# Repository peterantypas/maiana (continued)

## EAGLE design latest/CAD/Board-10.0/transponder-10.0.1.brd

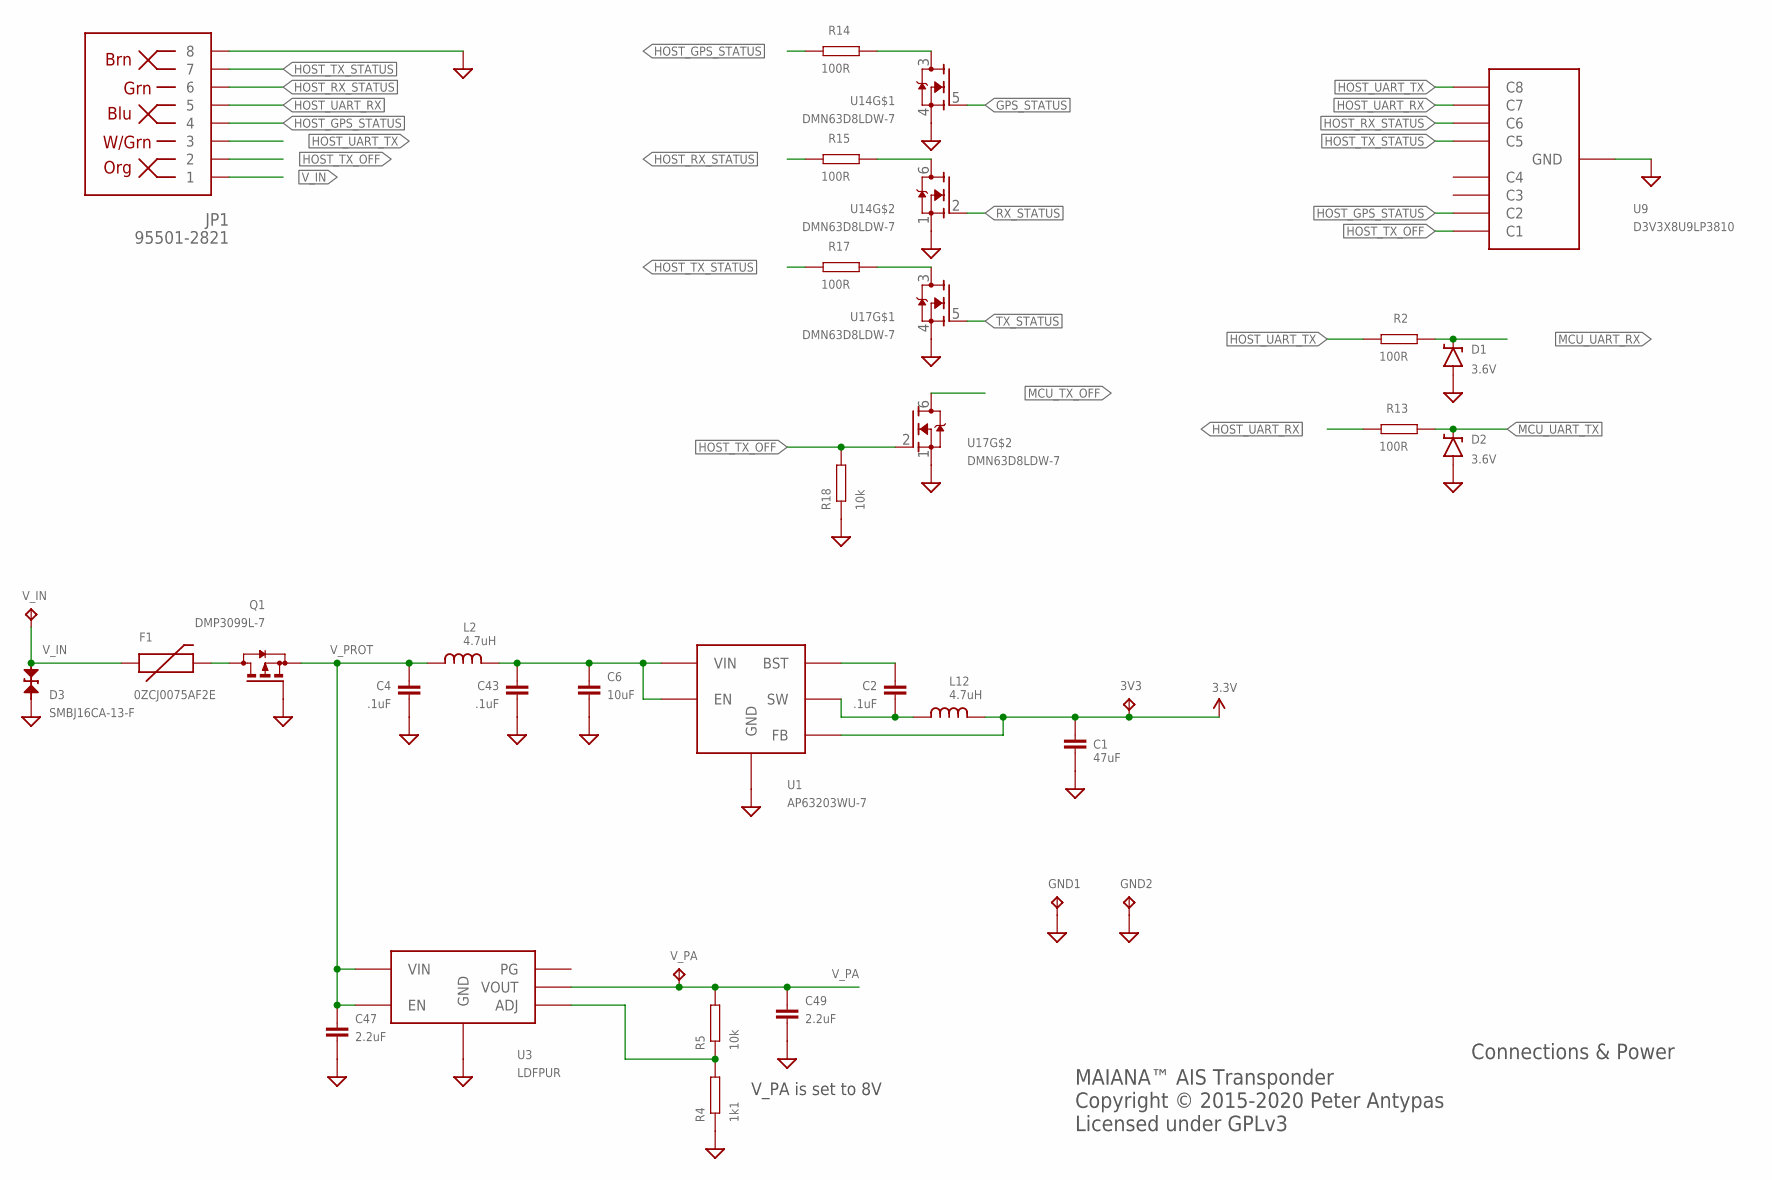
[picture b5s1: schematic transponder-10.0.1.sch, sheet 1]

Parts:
3V3: TPTP12R; TP12R
C1: 47uF; 1206; PARTNO CL31A476MQHNNNE
C2, C4, C43: .1uF; 0603; PARTNO EMK107B7104KAHT
C6: 10uF; 0805; PARTNO EMK212ABJ106KG-T
C47, C49: 2.2uF; 0603; PARTNO EMK107BJ225KA-T
D1, D2: 3.6V; SOD-323; PARTNO MM3Z3V6C
D3: SMBJ16CA-13-F; SMB-BIDIR; PARTNO SMBJ16CA-13-F
F1: 0ZCJ0075AF2E; PTC-1206; PARTNO 0ZCJ0075AF2E
GND1, GND2: TPTP12R; TP12R
JP1: 95501-2821; RJ45-8; PARTNO 95501-2821
L2, L12: 4.7uH; 0805; PARTNO MLZ2012M4R7WT000
Q1: DMP3099L-7; SOT23; PARTNO DMP3099L-7
R2, R13, R14, R15, R17: 100R; 0603; PARTNO RC0603JR-07100RL
R4: 1k1; 0603; PARTNO RC0603JR-071K1L
R5, R18: 10k; 0603; PARTNO RC0603JR-0710KL
U1: AP63203WU-7; SOT23-6
U3: LDFPUR; DFN-6; PARTNO LDFPUR
U9: D3V3X8U9LP3810; U-DFN3810-9(B)
U14, U17: DMN63D8LDW-7; SOT363; PARTNO DMN63D8LDW-7
V_IN: TPTP12R; TP12R
V_PA: TPTP12R; TP12R

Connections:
3.3V: 3V3.TP, C1.P$1 (1), L12.P$2 (2), U1.1 (FB); also elsewhere on the board
BST: C2.P$1 (1), U1.6 (BST)
GND: C1.P$2 (2), C4.P$2 (2), C6.P$2 (2), C43.P$2 (2), C47.P$2 (2), C49.P$2 (2), D1.A, D2.A, D3.C, GND1.TP, GND2.TP, JP1.8, Q1.1 (G), R4.P$1, R18.P$1, U1.4 (GND), U3.P$4 (GND), U3.P$7 (GND), U9.P$3 (GND), U14.1 (S), U14.4 (S), U17.1 (S), U17.4 (S); also elsewhere on the board
GPS_STATUS: U14.5 (G); also elsewhere on the board
HOST_GPS_STATUS: JP1.4, R14.P$2, U9.P$2 (C2)
HOST_RX_STATUS: JP1.6, R15.P$2, U9.P$7 (C6)
HOST_TX_OFF: JP1.2, R18.P$2, U9.P$1 (C1), U17.2 (G)
HOST_TX_STATUS: JP1.7, R17.P$2, U9.P$6 (C5)
HOST_UART_RX: JP1.5, R13.P$2, U9.P$8 (C7)
HOST_UART_TX: JP1.3, R2.P$2, U9.P$9 (C8)
MCU_TX_OFF: U17.6 (D); also elsewhere on the board
MCU_UART_RX: D1.C, R2.P$1; also elsewhere on the board
MCU_UART_TX: D2.C, R13.P$1; also elsewhere on the board
unnamed: R14.P$1, U14.3 (D)
unnamed: R15.P$1, U14.6 (D)
unnamed: R17.P$1, U17.3 (D)
unnamed: C6.P$1 (1), C43.P$1 (1), L2.P$2 (2), U1.2 (EN), U1.3 (VIN)
unnamed: R4.P$2, R5.P$1, U3.P$2 (ADJ)
unnamed: F1.2, Q1.3 (D)
RX_STATUS: U14.2 (G); also elsewhere on the board
SW: C2.P$2 (2), L12.P$1 (1), U1.5 (SW)
TX_STATUS: U17.5 (G); also elsewhere on the board
V_IN: D3.A, F1.1, JP1.1, V_IN.TP
V_PA: C49.P$1 (1), R5.P$2, U3.P$1 (VOUT), V_PA.TP; also elsewhere on the board
V_PROT: C4.P$1 (1), C47.P$1 (1), L2.P$1 (1), Q1.2 (S), U3.P$5 (EN), U3.P$6 (VIN)

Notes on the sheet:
Connections & Power
MAIANA™ AIS Transponder Copyright © 2015-2020 Peter Antypas Licensed under GPLv3
V_PA is set to 8V

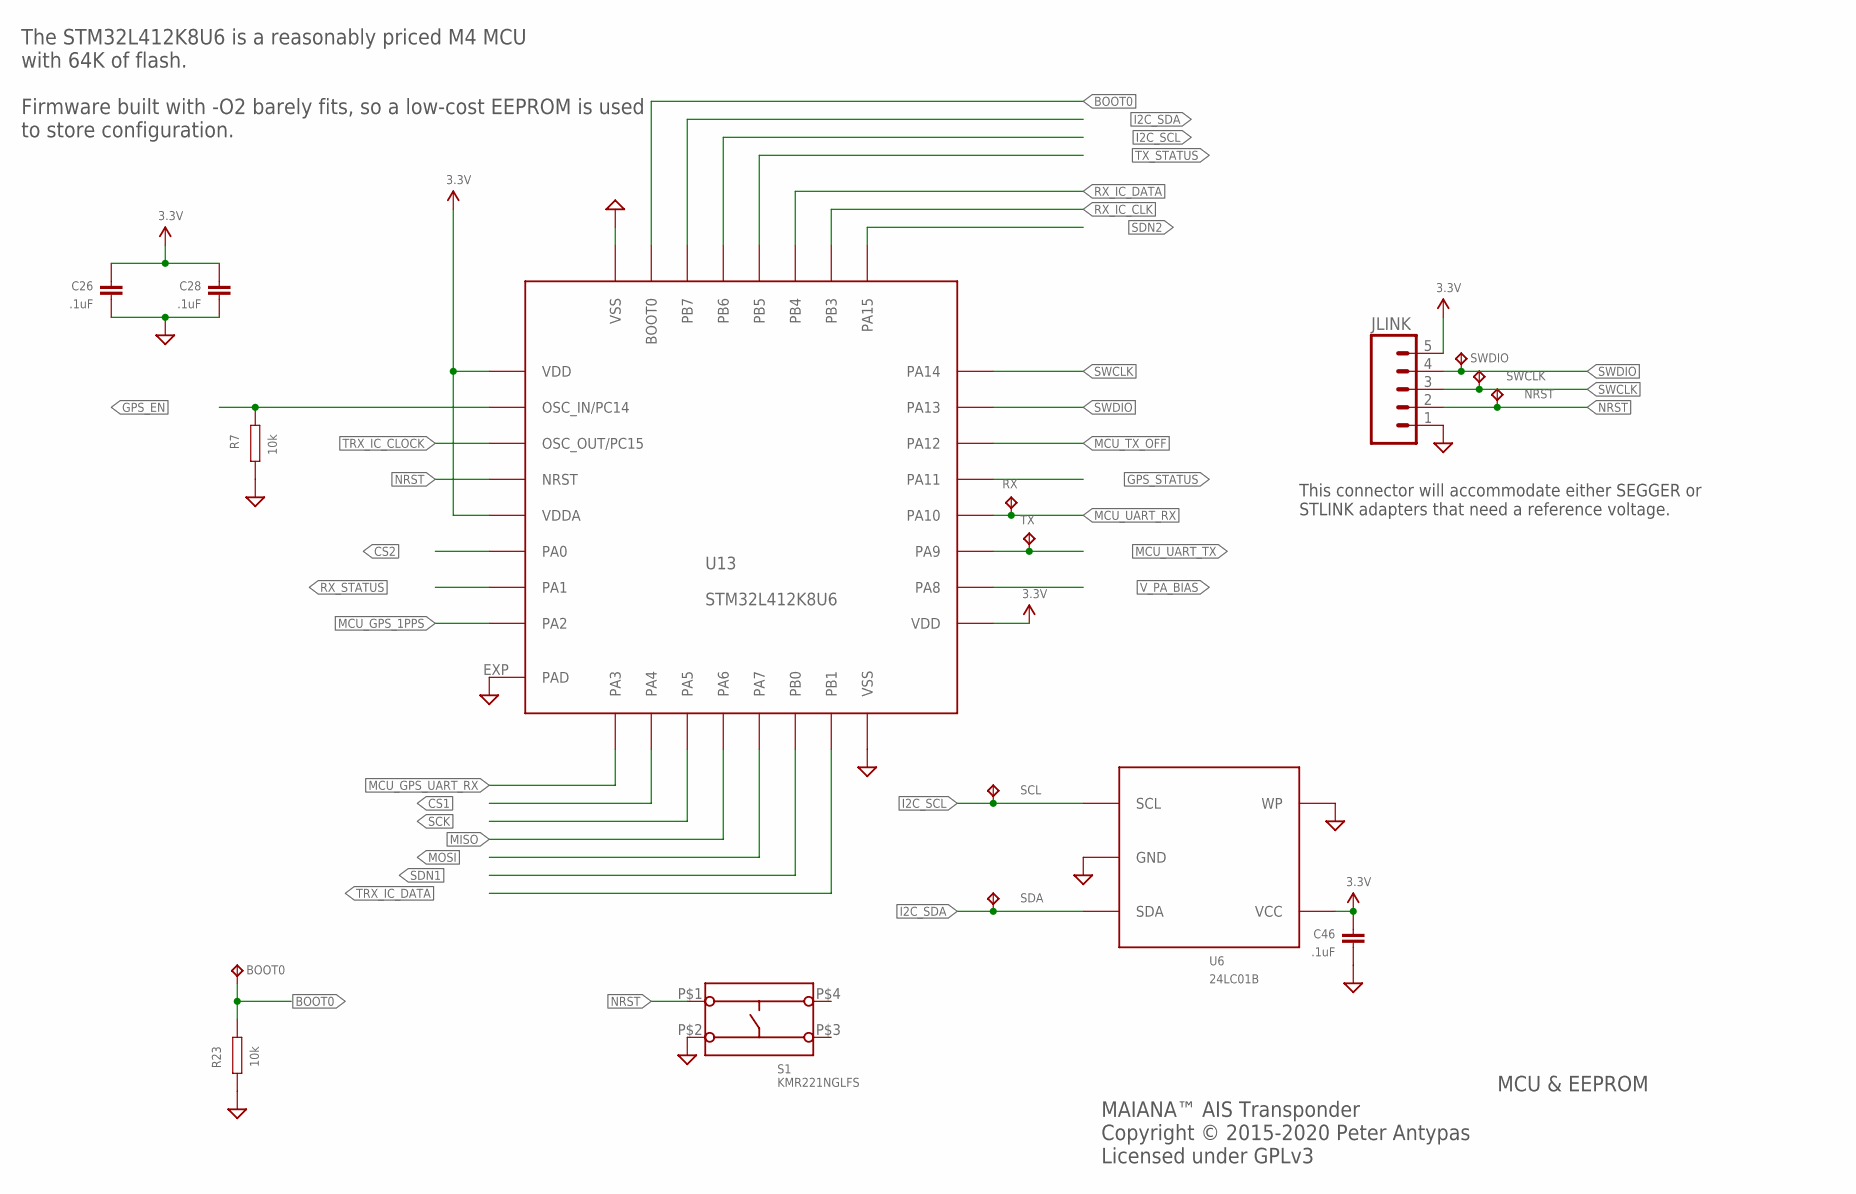
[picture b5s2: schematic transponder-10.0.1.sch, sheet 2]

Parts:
BOOT0: TPTP12R; TP12R
C26, C28, C46: .1uF; 0603; PARTNO EMK107B7104KAHT
JLINK: M05PTH; 1X05
NRST: TPTP12R; TP12R
R7, R23: 10k; 0603; PARTNO RC0603JR-0710KL
RX: TPTP12R; TP12R
S1: KMR221NGLFS
SCL: TPTP12R; TP12R
SDA: TPTP12R; TP12R
SWCLK: TPTP12R; TP12R
SWDIO: TPTP12R; TP12R
TX: TPTP12R; TP12R
U6: 24LC01B; SOT23-5; PARTNO 24LC01BT-I/OT
U13: STM32L412K8U6; QFN32; PARTNO STM32L412K8U6

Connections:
3.3V: C26.P$1 (1), C28.P$1 (1), C46.P$1 (1), JLINK.5, U6.4 (VCC), U13.1 (VDD), U13.5 (VDDA), U13.17 (VDD); also elsewhere on the board
BOOT0: BOOT0.TP, R23.P$1, U13.31 (BOOT0)
CS1: U13.10 (PA4); also elsewhere on the board
CS2: U13.6 (PA0); also elsewhere on the board
GND: C26.P$2 (2), C28.P$2 (2), C46.P$2 (2), JLINK.1, R7.P$2, R23.P$2, S1.P$2 (S2), U6.2 (GND), U6.5 (WP), U13.16 (VSS), U13.32 (VSS), U13.EXP (PAD); also elsewhere on the board
GPS_EN: R7.P$1, U13.2 (OSC_IN/PC14); also elsewhere on the board
GPS_STATUS: U13.21 (PA11); also elsewhere on the board
I2C_SCL: SCL.TP, U6.1 (SCL), U13.29 (PB6)
I2C_SDA: SDA.TP, U6.3 (SDA), U13.30 (PB7)
MCU_GPS_1PPS: U13.8 (PA2); also elsewhere on the board
MCU_GPS_UART_RX: U13.9 (PA3); also elsewhere on the board
MCU_TX_OFF: U13.22 (PA12); also elsewhere on the board
MCU_UART_RX: RX.TP, U13.20 (PA10); also elsewhere on the board
MCU_UART_TX: TX.TP, U13.19 (PA9); also elsewhere on the board
MISO: U13.12 (PA6); also elsewhere on the board
MOSI: U13.13 (PA7); also elsewhere on the board
NRST: JLINK.2, NRST.TP, S1.P$1 (S1), U13.4 (NRST)
RX_IC_CLK: U13.26 (PB3); also elsewhere on the board
RX_IC_DATA: U13.27 (PB4); also elsewhere on the board
RX_STATUS: U13.7 (PA1); also elsewhere on the board
SCK: U13.11 (PA5); also elsewhere on the board
SDN1: U13.14 (PB0); also elsewhere on the board
SDN2: U13.25 (PA15); also elsewhere on the board
SWCLK: JLINK.3, SWCLK.TP, U13.24 (PA14)
SWDIO: JLINK.4, SWDIO.TP, U13.23 (PA13)
TRX_IC_CLOCK: U13.3 (OSC_OUT/PC15); also elsewhere on the board
TRX_IC_DATA: U13.15 (PB1); also elsewhere on the board
TX_STATUS: U13.28 (PB5); also elsewhere on the board
V_PA_BIAS: U13.18 (PA8); also elsewhere on the board

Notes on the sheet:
MCU & EEPROM
MAIANA™ AIS Transponder Copyright © 2015-2020 Peter Antypas Licensed under GPLv3
The STM32L412K8U6 is a reasonably priced M4 MCU with 64K of flash. Firmware built with -O2 barely fits, so a low-cost EEPROM is used to store configuration.
This connector will accommodate either SEGGER or STLINK adapters that need a reference voltage.

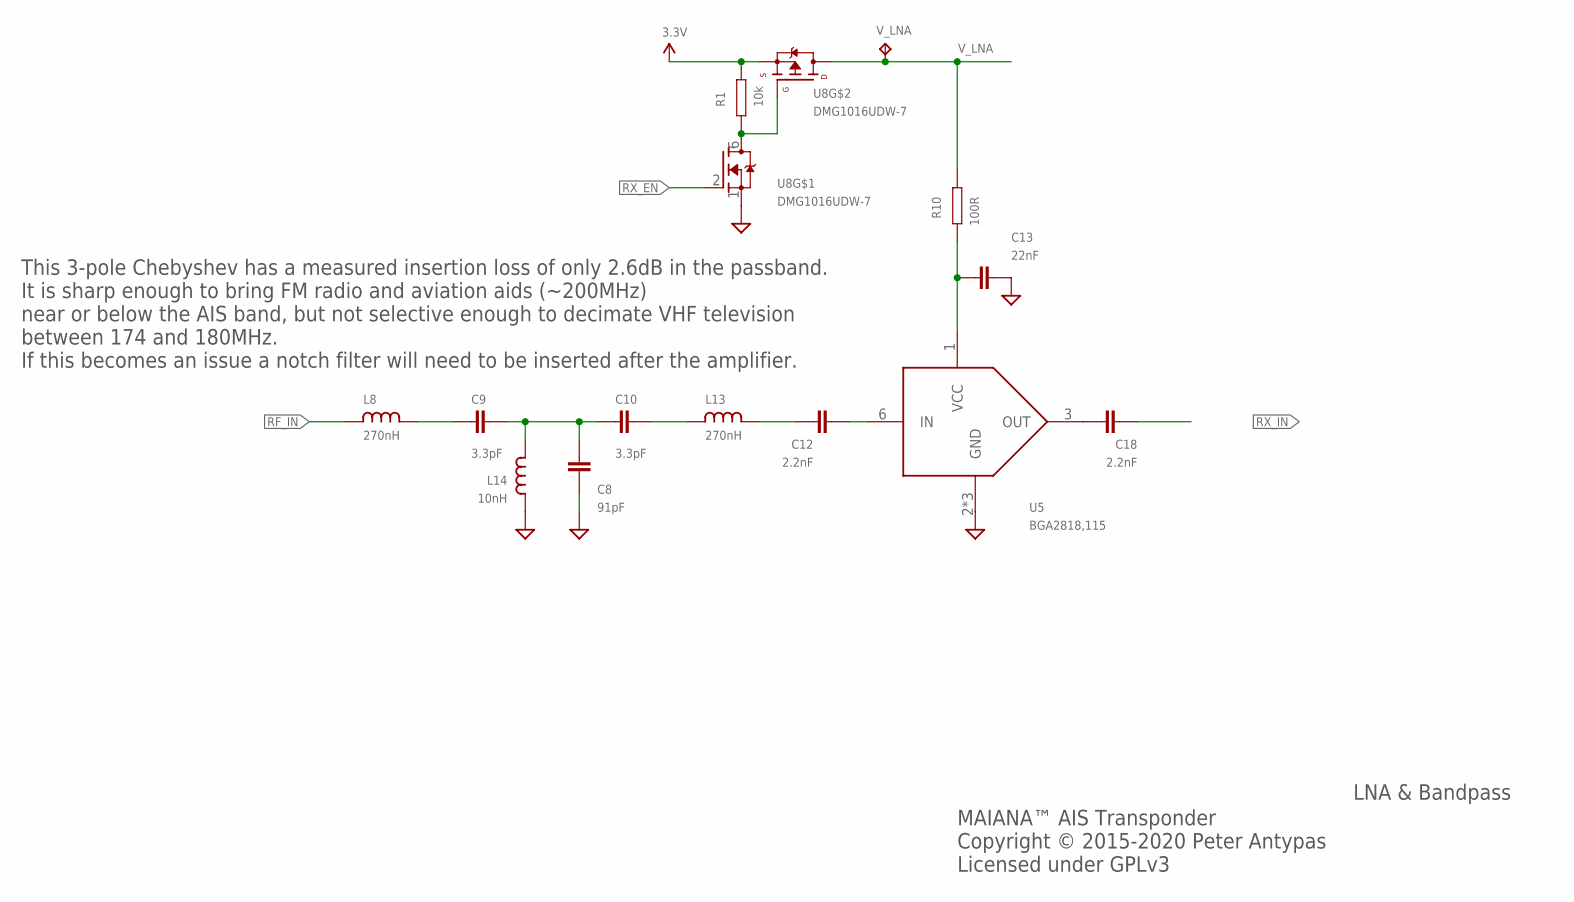
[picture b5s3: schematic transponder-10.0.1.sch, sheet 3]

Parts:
C8: 91pF; 0603; PARTNO GRM1885C2A910JA01D
C9, C10: 3.3pF; 0603; PARTNO GRM1885C1H3R3BA01D
C12, C18: 2.2nF; 0603; PARTNO GRM1885C1H222JA01J
C13: 22nF; 0603; PARTNO GRM188R71E223KA01D
L8, L13: 270nH; 0603; PARTNO LQW18ANR27J00D
L14: 10nH; 0603; PARTNO LQW18AN10NG00D
R1: 10k; 0603; PARTNO RC0603JR-0710KL
R10: 100R; 0603; PARTNO RC0603JR-07100RL
U5: BGA2818,115; SOT363; PARTNO BGA2818,115
U8: DMG1016UDW-7; SOT363
V_LNA: TPTP12R; TP12R

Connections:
3.3V: R1.P$2, U8.4 (S); also elsewhere on the board
GND: C8.P$2 (2), C13.P$2 (2), L14.P$1 (1), U5.2 (GND), U5.4 (GND), U5.5 (GND), U8.1 (S); also elsewhere on the board
unnamed: C12.P$2 (2), U5.6 (IN)
unnamed: C9.P$1 (1), L8.P$2 (2)
unnamed: C8.P$1 (1), C9.P$2 (2), C10.P$1 (1), L14.P$2 (2)
unnamed: C10.P$2 (2), L13.P$1 (1)
unnamed: C12.P$1 (1), L13.P$2 (2)
unnamed: C13.P$1 (1), R10.P$2, U5.1 (VCC)
unnamed: C18.P$1 (1), U5.3 (OUT)
unnamed: R1.P$1, U8.5 (G), U8.6 (D)
RF_IN: L8.P$1 (1); also elsewhere on the board
RX_EN: U8.2 (G); also elsewhere on the board
RX_IN: C18.P$2 (2); also elsewhere on the board
V_LNA: R10.P$1, U8.3 (D), V_LNA.TP

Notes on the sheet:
LNA & Bandpass
MAIANA™ AIS Transponder Copyright © 2015-2020 Peter Antypas Licensed under GPLv3
This 3-pole Chebyshev has a measured insertion loss of only 2.6dB in the passband. It is sharp enough to bring FM radio and aviation aids (~200MHz) near or below the AIS band, but not selective enough to decimate VHF television between 174 and 180MHz. If this becomes an issue a notch filter will ne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

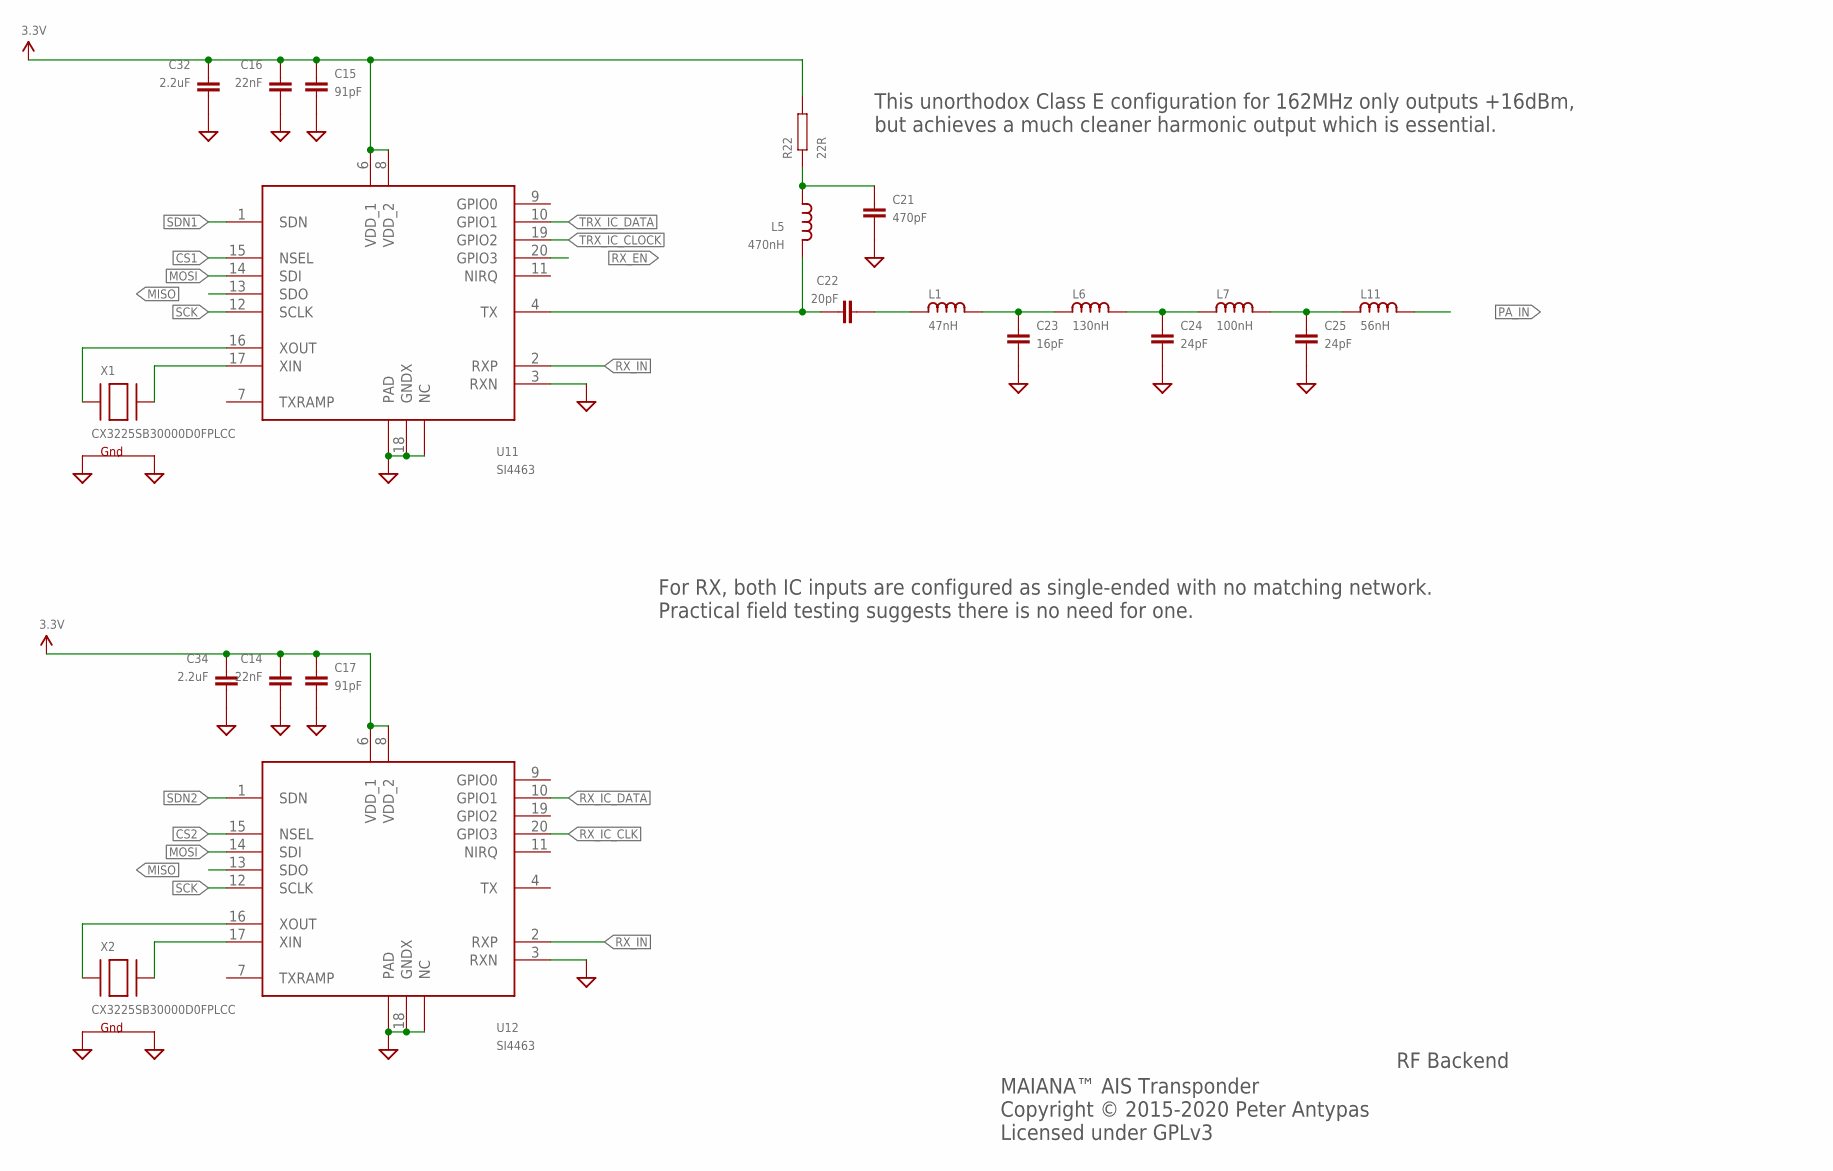
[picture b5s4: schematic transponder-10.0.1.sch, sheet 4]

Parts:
C14, C16: 22nF; 0603; PARTNO GRM188R71E223KA01D
C15, C17: 91pF; 0603; PARTNO GRM1885C2A910JA01D
C21: 470pF; 0603; PARTNO GRM1885C1H471JA01D
C22: 20pF; 0603; PARTNO GRM1885C1H200JA01D
C23: 16pF; 0603; PARTNO GCM1885C2A160JA16D
C24, C25: 24pF; 0603; PARTNO GRM1885C2A240JA01D
C32, C34: 2.2uF; 0603; PARTNO EMK107BJ225KA-T
L1: 47nH; 0603; PARTNO LQW18AN47NG00D
L5: 470nH; 0603; PARTNO HK1608R47J-T
L6: 130nH; 0603; PARTNO LQW18ANR13J00D
L7: 100nH; 0603; PARTNO LQW18ANR10G00D
L11: 56nH; 0603; PARTNO LQW18AN56NG00D
R22: 22R; 0603; PARTNO RC0603JR-0722RL
U11, U12: SI4463; PARTNO SI4463-C2A-GMR
X1, X2: CX3225SB30000D0FPLCC; NX3225; PARTNO CX3225SB30000D0FPLCC

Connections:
3.3V: C14.P$1 (1), C15.P$1 (1), C16.P$1 (1), C17.P$1 (1), C32.P$1 (1), C34.P$1 (1), R22.P$2, U11.6 (VDD_1), U11.8 (VDD_2), U12.6 (VDD_1), U12.8 (VDD_2); also elsewhere on the board
CS1: U11.15 (NSEL); also elsewhere on the board
CS2: U12.15 (NSEL); also elsewhere on the board
GND: C14.P$2 (2), C15.P$2 (2), C16.P$2 (2), C17.P$2 (2), C21.P$2 (2), C23.P$2 (2), C24.P$2 (2), C25.P$2 (2), C32.P$2 (2), C34.P$2 (2), U11.3 (RXN), U11.5 (NC), U11.18 (GNDX), U11.EXP (PAD), U12.3 (RXN), U12.5 (NC), U12.18 (GNDX), U12.EXP (PAD), X1.2 (G2), X1.4 (G1), X2.2 (G2), X2.4 (G1); also elsewhere on the board
MISO: U11.13 (SDO), U12.13 (SDO); also elsewhere on the board
MOSI: U11.14 (SDI), U12.14 (SDI); also elsewhere on the board
unnamed: C24.P$1 (1), L6.P$2 (2), L7.P$1 (1)
unnamed: C25.P$1 (1), L7.P$2 (2), L11.P$1 (1)
unnamed: C23.P$1 (1), L1.P$2 (2), L6.P$1 (1)
unnamed: U12.16 (XOUT), X2.1 (X1)
unnamed: U12.17 (XIN), X2.3 (X2)
unnamed: U11.16 (XOUT), X1.1 (X1)
unnamed: U11.17 (XIN), X1.3 (X2)
unnamed: C22.P$1 (1), L5.P$2 (2), U11.4 (TX)
unnamed: C21.P$1 (1), L5.P$1 (1), R22.P$1
unnamed: C22.P$2 (2), L1.P$1 (1)
PA_IN: L11.P$2 (2); also elsewhere on the board
RX_EN: U11.20 (GPIO3); also elsewhere on the board
RX_IC_CLK: U12.20 (GPIO3); also elsewhere on the board
RX_IC_DATA: U12.10 (GPIO1); also elsewhere on the board
RX_IN: U11.2 (RXP), U12.2 (RXP); also elsewhere on the board
SCK: U11.12 (SCLK), U12.12 (SCLK); also elsewhere on the board
SDN1: U11.1 (SDN); also elsewhere on the board
SDN2: U12.1 (SDN); also elsewhere on the board
TRX_IC_CLOCK: U11.19 (GPIO2); also elsewhere on the board
TRX_IC_DATA: U11.10 (GPIO1); also elsewhere on the board

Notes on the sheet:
RF Backend
MAIANA™ AIS Transponder Copyright © 2015-2020 Peter Antypas Licensed under GPLv3
This unorthodox Class E configuration for 162MHz only outputs +16dBm, but achieves a much cleaner harmonic output which is essential.
For RX, both IC inputs are configured as single-ended with no matching network. Practical field testing suggests there is no need for one.

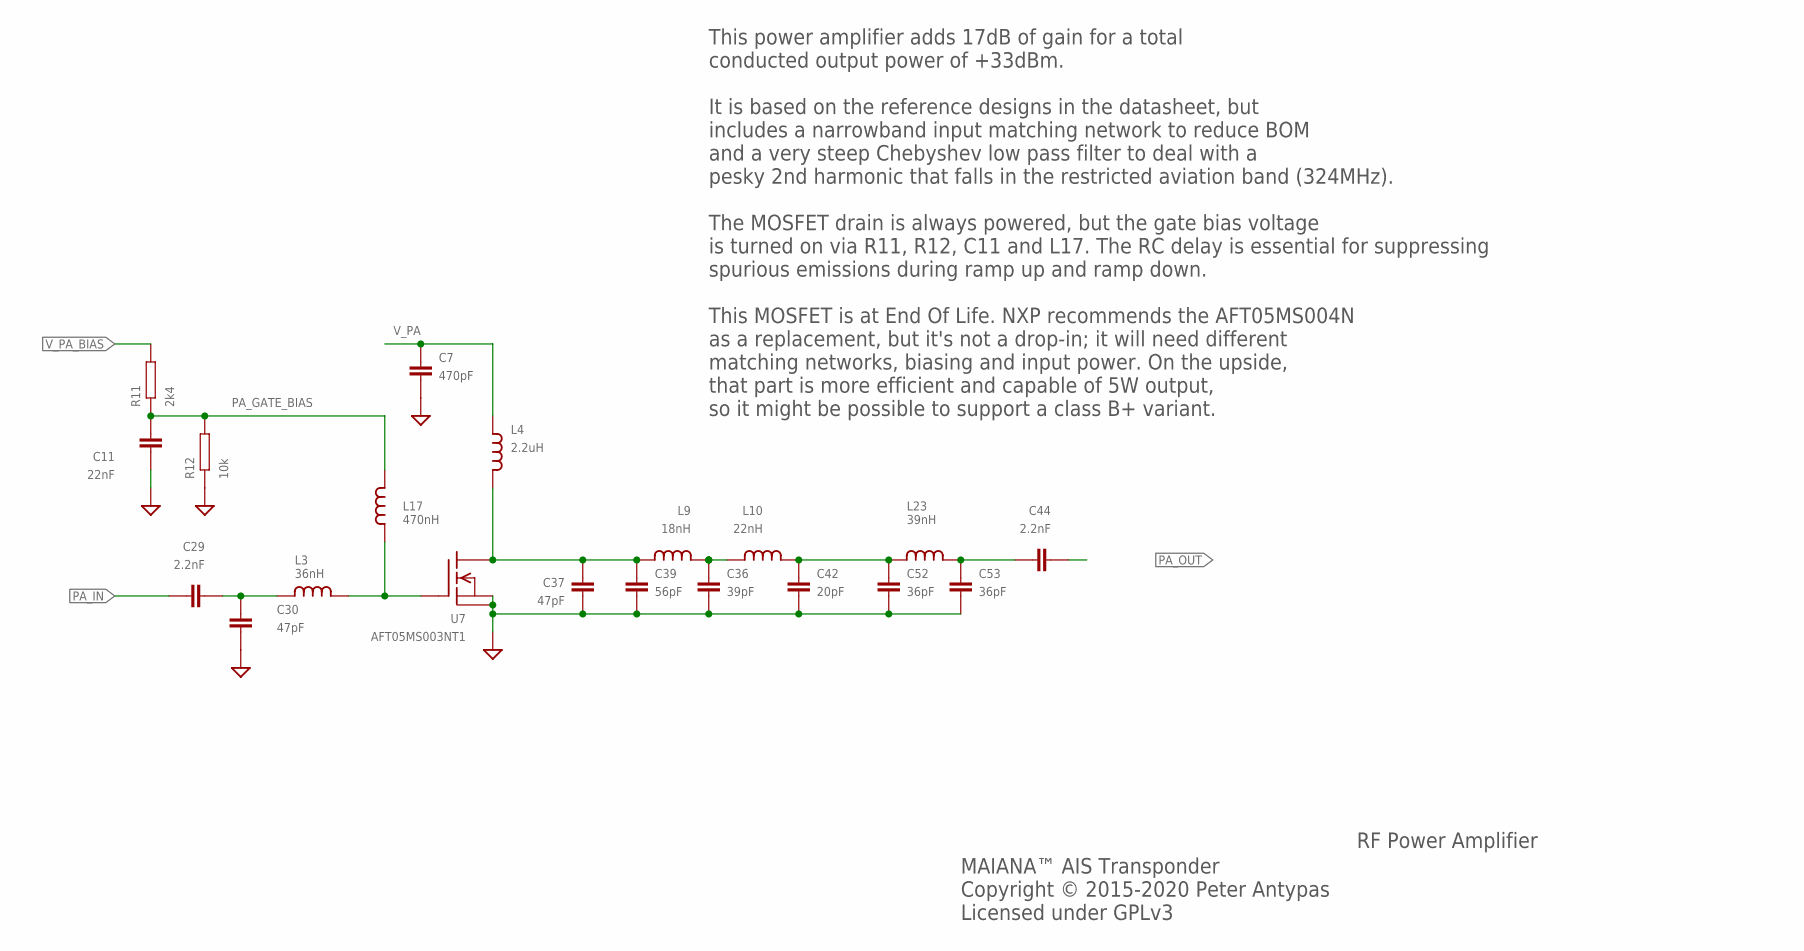
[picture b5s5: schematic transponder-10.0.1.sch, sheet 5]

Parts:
C7: 470pF; 0603; PARTNO GRM1885C1H471JA01D
C11: 22nF; 0603; PARTNO GRM188R71E223KA01D
C29, C44: 2.2nF; 0603; PARTNO GRM1885C1H222JA01J
C30, C37: 47pF; 0603; PARTNO GRM1885C1H470JA01J
C36: 39pF; 0603; PARTNO GRM1885C1H390JA01D
C39: 56pF; 0603; PARTNO GRM1885C1H560JA01D
C42: 20pF; 0603; PARTNO GRM1885C1H200JA01D
C52, C53: 36pF; 0603; PARTNO 06035A360JAT2A
L3: 36nH; 0603; PARTNO LQW18AN36NG00D
L4: 2.2uH; 0805; PARTNO BRC2012T2R2MD
L9: 18nH; 0603; PARTNO LQW18AN18NG00D
L10: 22nH; 0603; PARTNO LQW18AN22NJ00D
L17: 470nH; 1206; PARTNO HK1608R47J-T
L23: 39nH; 0603; PARTNO LQW18AN39NG00D
R11: 2k4; 0603; PARTNO RC0603JR-072K4L
R12: 10k; 0603; PARTNO RC0603JR-0710KL
U7: AFT05MS003NT1; SOT-89; PARTNO AFT05MS003NT1

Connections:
GND: C7.P$2 (2), C11.P$2 (2), C30.P$2 (2), C36.P$2 (2), C37.P$2 (2), C39.P$2 (2), C42.P$2 (2), C52.P$2 (2), C53.P$2 (2), R12.P$1, U7.2 (S), U7.2@1 (PAD); also elsewhere on the board
unnamed: C37.P$1 (1), C39.P$1 (1), L4.P$2 (2), L9.P$1 (1), U7.3 (D)
unnamed: L3.P$2 (2), L17.P$1 (1), U7.1 (G)
unnamed: C36.P$1 (1), L9.P$2 (2), L10.P$1 (1)
unnamed: C29.P$2 (2), C30.P$1 (1), L3.P$1 (1)
unnamed: C42.P$1 (1), C52.P$1 (1), L10.P$2 (2), L23.P$1 (1)
unnamed: C44.P$1 (1), C53.P$1 (1), L23.P$2 (2)
PA_GATE_BIAS: C11.P$1 (1), L17.P$2 (2), R11.P$1, R12.P$2
PA_IN: C29.P$1 (1); also elsewhere on the board
PA_OUT: C44.P$2 (2); also elsewhere on the board
V_PA: C7.P$1 (1), L4.P$1 (1); also elsewhere on the board
V_PA_BIAS: R11.P$2; also elsewhere on the board

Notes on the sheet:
RF Power Amplifier
MAIANA™ AIS Transponder Copyright © 2015-2020 Peter Antypas Licensed under GPLv3
This power amplifier adds 17dB of gain for a total conducted output power of +33dBm. It is based on the reference designs in the datasheet, but includes a narrowband input matching network to reduce BOM and a very steep Chebyshev low pass filter to deal with a pesky 2nd harmonic that falls in the r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

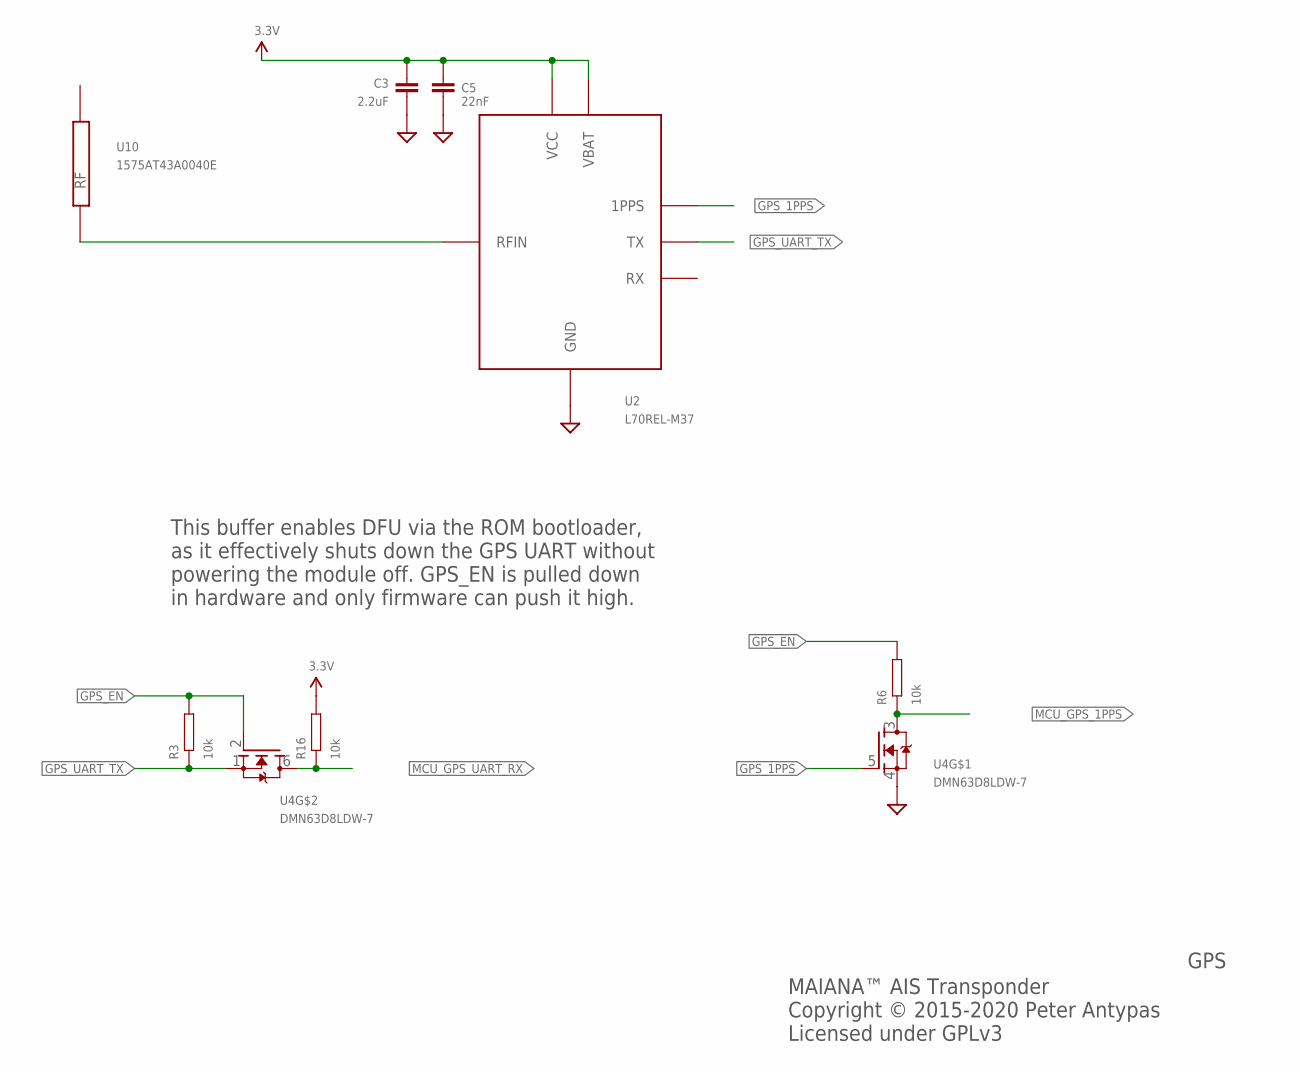
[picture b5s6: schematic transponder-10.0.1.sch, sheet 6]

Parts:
C3: 2.2uF; 0603; PARTNO EMK107BJ225KA-T
C5: 22nF; 0603; PARTNO GRM188R71E223KA01D
R3, R6, R16: 10k; 0603; PARTNO RC0603JR-0710KL
U2: L70REL-M37; GPS_MODULE; PARTNO L70B-M39
U4: DMN63D8LDW-7; SOT363; PARTNO DMN63D8LDW-7
U10: 1575AT43A0040E; PARTNO 1575AT43A0040E

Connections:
3.3V: C3.P$1 (1), C5.P$1 (1), R16.P$2, U2.P$6 (VBAT), U2.P$8 (VCC); also elsewhere on the board
GND: C3.P$2 (2), C5.P$2 (2), U2.P$1 (GND), U2.P$10 (GND), U2.P$12 (GND), U4.4 (S); also elsewhere on the board
GPS_1PPS: U2.P$4 (1PPS), U4.5 (G)
GPS_EN: R3.P$2, R6.P$2, U4.2 (G); also elsewhere on the board
GPS_UART_TX: R3.P$1, U2.P$2 (TX), U4.1 (S)
MCU_GPS_1PPS: R6.P$1, U4.3 (D); also elsewhere on the board
MCU_GPS_UART_RX: R16.P$1, U4.6 (D); also elsewhere on the board
unnamed: U2.P$11 (RFIN), U10.P$1 (RF)

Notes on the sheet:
GPS
MAIANA™ AIS Transponder Copyright © 2015-2020 Peter Antypas Licensed under GPLv3
This buffer enables DFU via the ROM bootloader, as it effectively shuts down the GPS UART without powering the module off. GPS_EN is pulled down in hardware and only firmware can push it high.

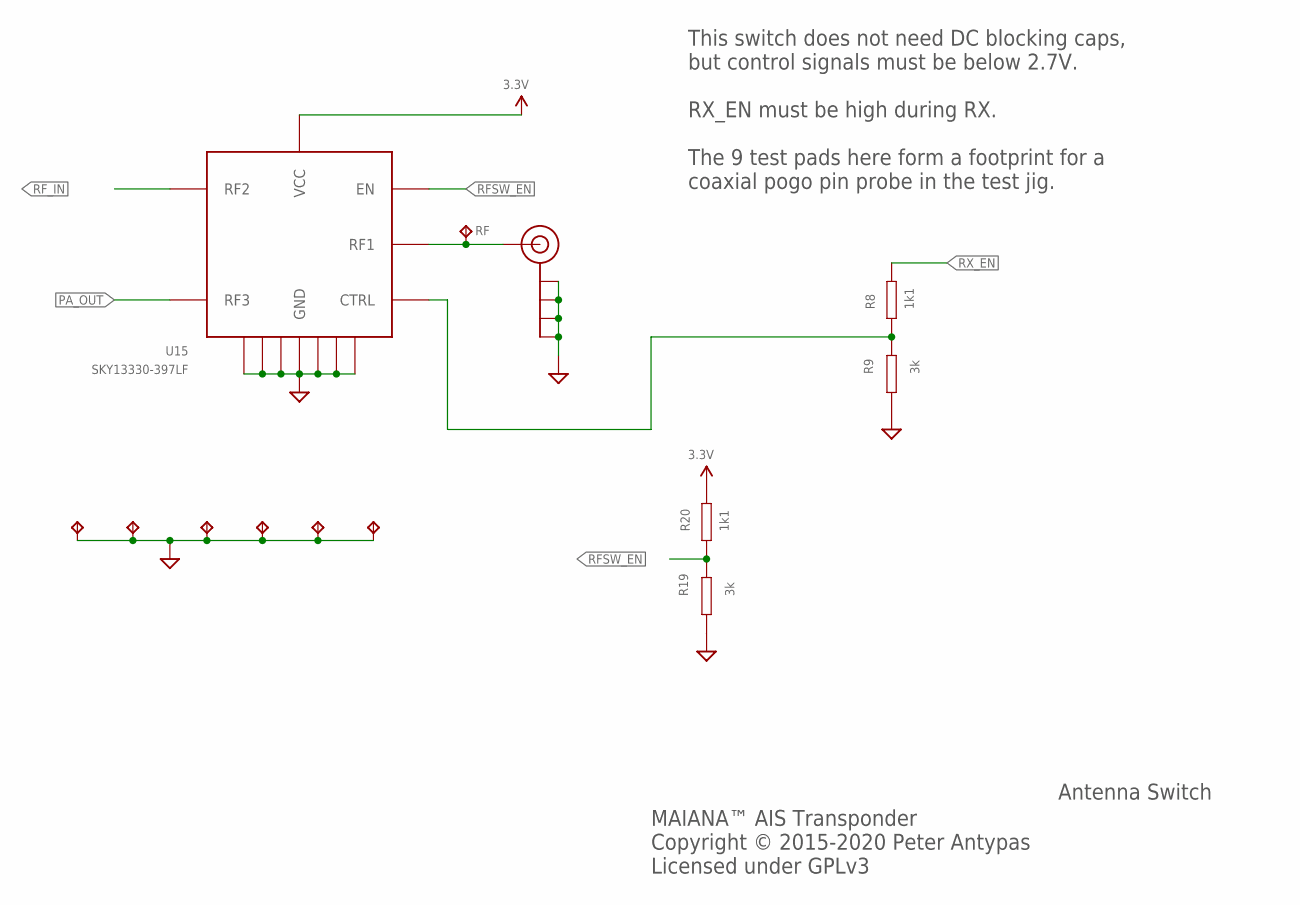
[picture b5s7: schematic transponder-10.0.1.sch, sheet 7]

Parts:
J$1: SMA_EDGE; SMA-EDGE
R8, R20: 1k1; 0603; PARTNO RC0603JR-071K1L
R9, R19: 3k; 0603; PARTNO RC0603JR-073KL
RF: TPTP10R; TP10R
SWDIO1, SWDIO2, SWDIO3, SWDIO4, SWDIO5, SWDIO6: TPTP12R; TP12R
U15: SKY13330-397LF; QFN12; PARTNO SKY13330-397LF

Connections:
1V8: R8.P$1, R9.P$2, U15.P$7 (CTRL)
3.3V: R20.P$2, U15.P$9 (VCC); also elsewhere on the board
GND: J$1.GND@0 (GND), J$1.GND@1 (GND), J$1.GND@2 (GND), J$1.GND@3 (GND), R9.P$1, R19.P$1, SWDIO1.TP, SWDIO2.TP, SWDIO3.TP, SWDIO4.TP, SWDIO5.TP, SWDIO6.TP, U15.P$1 (GND), U15.P$3 (GND), U15.P$4 (GND), U15.P$6 (GND), U15.P$10 (GND), U15.P$12 (GND), U15.P$13 (GND); also elsewhere on the board
unnamed: J$1.SIG (SIGNAL), RF.TP, U15.P$2 (RF1)
PA_OUT: U15.P$5 (RF3); also elsewhere on the board
RFSW_EN: R19.P$2, R20.P$1, U15.P$8 (EN)
RF_IN: U15.P$11 (RF2); also elsewhere on the board
RX_EN: R8.P$2; also elsewhere on the board

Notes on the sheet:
Antenna Switch
MAIANA™ AIS Transponder Copyright © 2015-2020 Peter Antypas Licensed under GPLv3
This switch does not need DC blocking caps, but control signals must be below 2.7V. RX_EN must be high during RX. The 9 test pads here form a footprint for a coaxial pogo pin probe in the test jig.

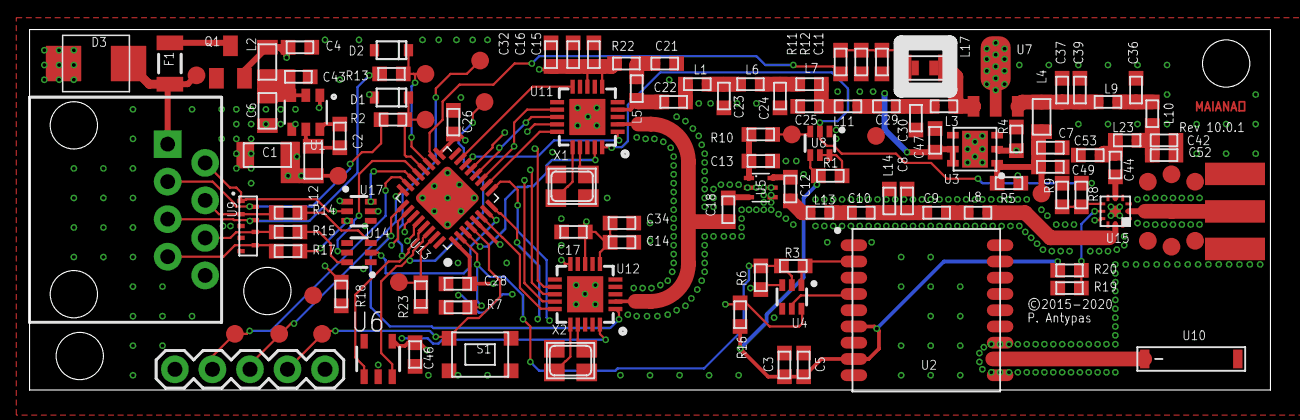
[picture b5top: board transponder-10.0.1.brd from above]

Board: 4 copper layers, 84.0 x 24.4 mm, 126 parts (0 on the bottom side), 83 nets.

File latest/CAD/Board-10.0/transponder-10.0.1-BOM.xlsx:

Qty | PartNo | Description | Value | Package | Reference Designators
1 | 0ZCJ0075AF2E | Resettable Fuse PTC | 0ZCJ0075AF2E | PTC-1206 | F1
1 | 1575AT43A0040E | SMD Ceramic GNSS Antenna | 1575AT43A0040E | 1575AT43A0040E | U10
2 | 06035A360JAT2A | Standard SMD capacitor | 36pF | 0603 | C52, C53
1 | 95501-2821 | RJ45 Jack | RJ45 | RJ45-8 | JP1
1 | AFT05MS003NT1 |  | AFT05MS003NT1 | SOT-89 | U7
1 | AP63203WU-7 | Low EMI buck converter | AP63203WU-7 | SOT23-6 | U1
1 | BGA2818,115 | MMIC Wideband Amplifier | BGA2818,115 | SOT363 | U5
1 | BRC2012T2R2MD | Standard SMD inductor | 2.2uH | 0805 | L4
1 | CL31A476MQHNNNE | Standard SMD capacitor | 47uF | 1206 | C1
2 | CX3225SB30000D0FPLCC | Classic 4-pin 3.2 x 2.5mm crystal | CX3225SB30000D0FPLCC | NX3225 | X1, X2
1 | D3V3X8U9LP3810 | 8 CHANNEL LOW CAPACITANCE TVS DIODE ARRAY | D3V3X8U9LP3810 | U-DFN3810-9(B) | U9
1 | DMG1016UDW-7 | N/P Channel MOSFET pair | DMG1016UDW-7 | SOT363 | U8
3 | DMN63D8LDW-7 | Dual N-Channel MOSFET | DMN63D8LDW-7 | SOT363 | U4, U14, U17
1 | DMP3099L-7 | P-CHANNEL MOS FET | DMP3099L-7 | SOT23 | Q1
5 | EMK107B7104KAHT | Standard SMD capacitor | .1uF | 0603 | C2, C4, C26, C28, C43
5 | EMK107BJ225KA-T | Standard SMD capacitor | 2.2uF | 0603 | C3, C32, C34, C47, C49
1 | EMK212ABJ106KG-T | Standard SMD capacitor | 10uF | 0805 | C6
1 | GCM1885C2A160JA16D | Standard SMD capacitor | 16pF | 0603 | C23
5 | GRM188R71E223KA01D | Standard SMD capacitor | 22nF | 0603 | C5, C11, C13, C14, C16
2 | GRM1885C1H3R3BA01D | Standard SMD capacitor | 3.3pF | 0603 | C9, C10
2 | GRM1885C1H200JA01D | Standard SMD capacitor | 20pF | 0603 | C22, C42
4 | GRM1885C1H222JA01J | Standard SMD capacitor | 2.2nF | 0603 | C12, C18, C29, C44
1 | GRM1885C1H390JA01D | Standard SMD capacitor | 39pF | 0603 | C36
2 | GRM1885C1H470JA01J | Standard SMD capacitor | 47pF | 0603 | C30, C37
2 | GRM1885C1H471JA01D | Standard SMD capacitor | 470pF | 0603 | C7, C21
1 | GRM1885C1H560JA01D | Standard SMD capacitor | 56pF | 0603 | C39
2 | GRM1885C2A240JA01D | Standard SMD capacitor | 24pF | 0603 | C24, C25
3 | GRM1885C2A910JA01D | Standard SMD capacitor | 91pF | 0603 | C8, C15, C17
2 | HK1608R47J-T | Standard SMD inductor | 470nH | 0603 | L5, L17
1 | L70B-M39 | GPS Module | L70REL-M37 | GPS_MODULE | U2
1 | LDFPUR | Low Noise Adjustable LDO (1A max) | LDFPUR | DFN-6 | U3
1 | LQW18AN10NG00D | Standard SMD inductor | 10nH | 0603 | L14
1 | LQW18AN18NG00D | Standard SMD inductor | 18nH | 0603 | L9
1 | LQW18AN22NJ00D | Standard SMD inductor | 22nH | 0603 | L10
1 | LQW18AN36NG00D | Standard SMD inductor | 36nH | 0603 | L3
1 | LQW18AN39NG00D | Standard SMD inductor | 39nH | 0603 | L23
1 | LQW18AN47NG00D | Standard SMD inductor | 47nH | 0603 | L1
1 | LQW18AN56NG00D | Standard SMD inductor | 56nH | 0603 | L11
1 | LQW18ANR10G00D | Standard SMD inductor | 100nH | 0603 | L7
1 | LQW18ANR13J00D | Standard SMD inductor | 130nH | 0603 | L6
2 | LQW18ANR27J00D | Standard SMD inductor | 270nH | 0603 | L8, L13
2 | MLZ2012M4R7WT000 | Standard SMD inductor | 4.7uH | 0805 | L2, L12
2 | MM3Z3V6C | Zener Diode | 3.3V | SOD-323 | D1, D2
3 | RC0603JR-071K1L | Standard SMD resistor | 1k1 | 0603 | R4, R8, R20
1 | RC0603JR-072K4L | Standard SMD resistor | 2k4 | 0603 | R11
2 | RC0603JR-073KL | Standard SMD resistor | 3k | 0603 | R9, R19
9 | RC0603JR-0710KL | Standard SMD resistor | 10k | 0603 | R1, R3, R5, R6, R7, R12, R16, R18, R23
1 | RC0603JR-0722RL | Standard SMD resistor | 22R | 0603 | R22
6 | RC0603JR-07100RL | Standard SMD resistor | 100R | 0603 | R2, R10, R13, R14, R15, R17
2 | SI4463-C2A-GMR |  | SI4463 | SI4463 | U11, U12
1 | SKY13330-397LF | SP2T RF Switch | SKY13330-397LF | QFN12 | U15
1 | SMBJ16CA-13-F | Bidirectional TVS diode | SMBJ16CA-13-F | SMB-BIDIR | D3
1 | STM32L412K8U6 |  | STM32L412K8U6 | QFN32 | U13
